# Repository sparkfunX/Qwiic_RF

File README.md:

# Qwiic_RF
LoRa Radio for the Qwiic System

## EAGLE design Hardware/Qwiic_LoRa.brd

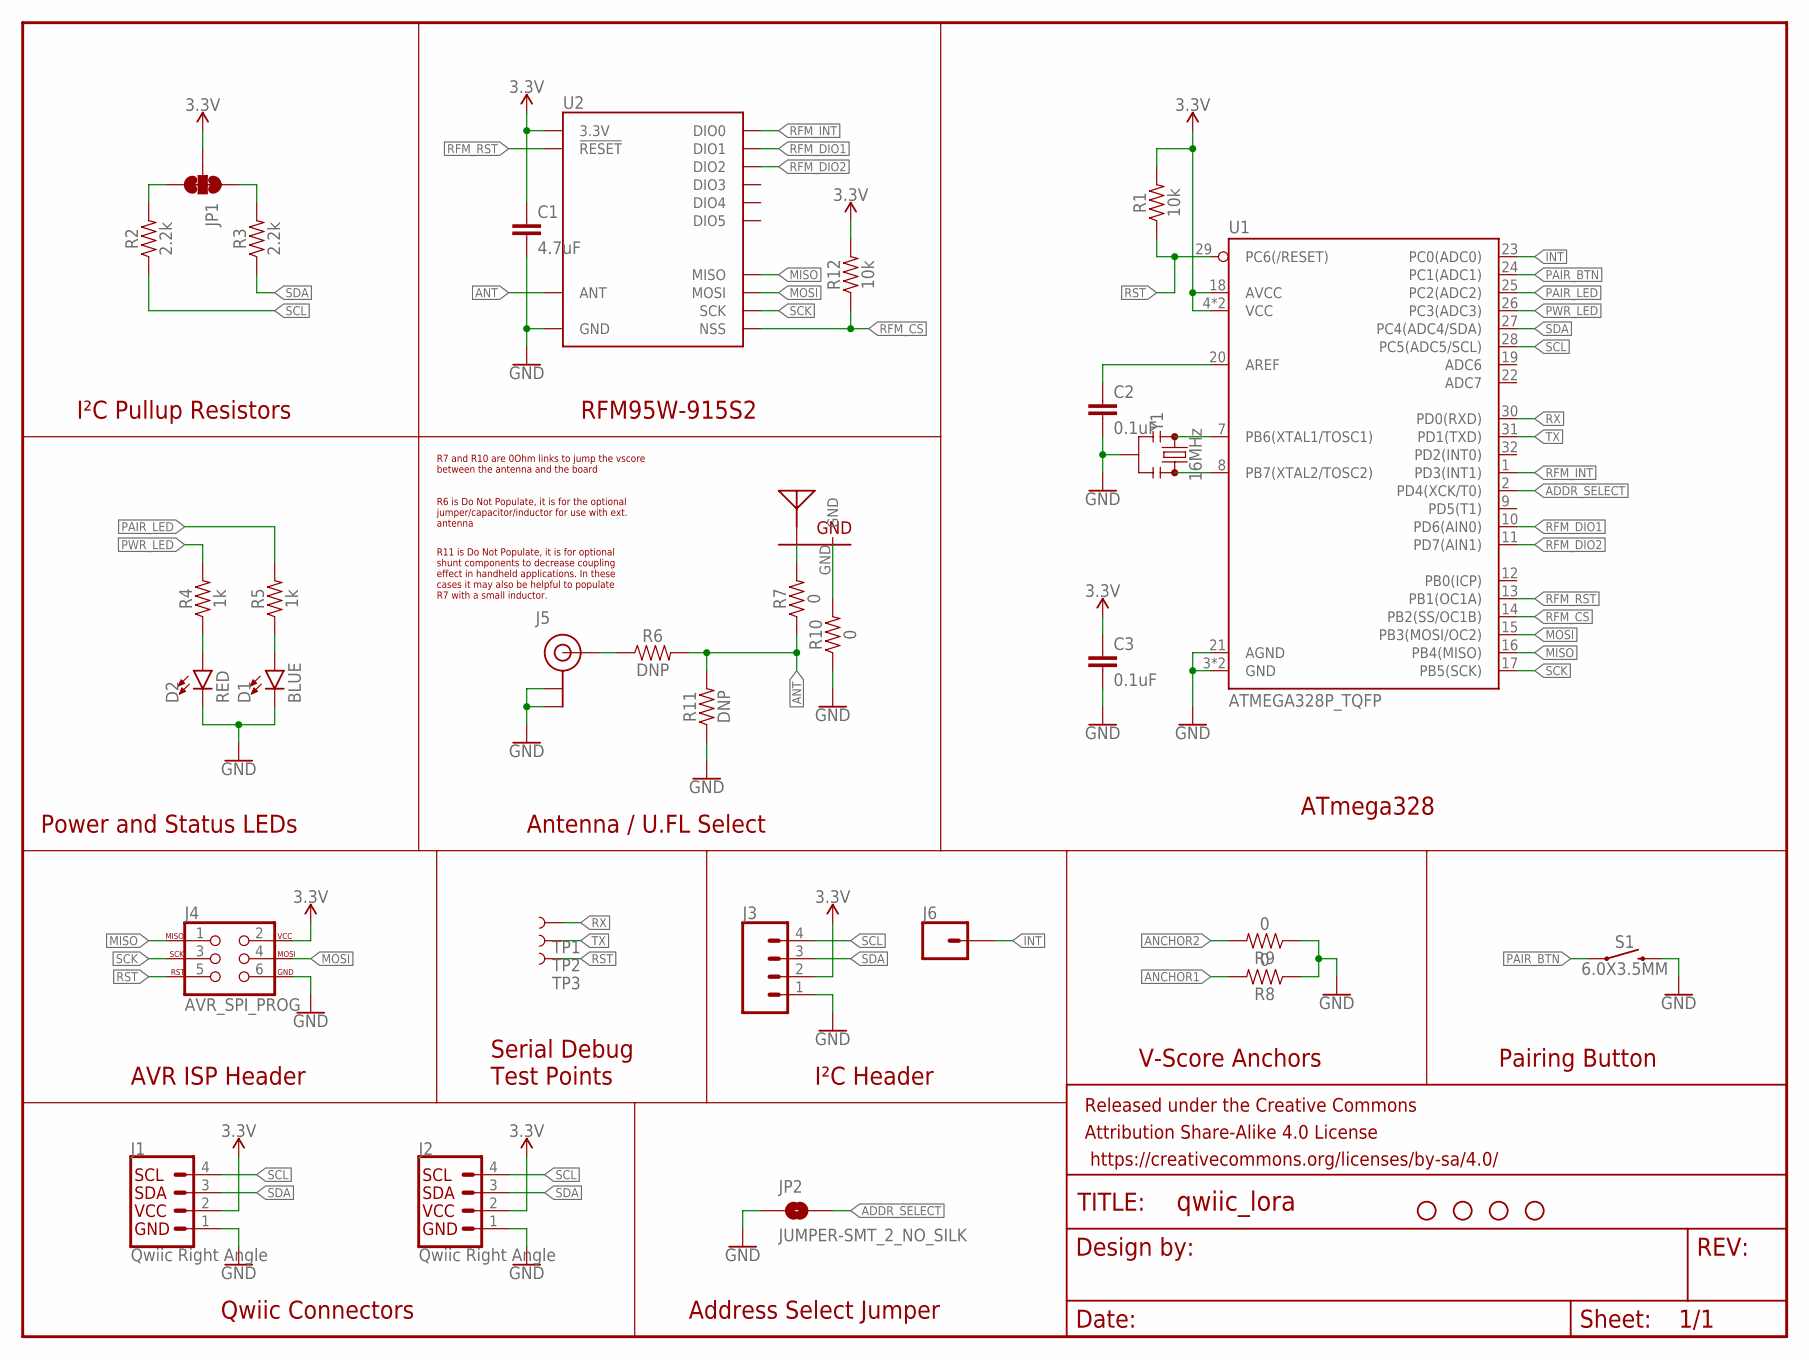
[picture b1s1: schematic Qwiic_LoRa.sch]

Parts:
C1: 4.7uF; 0603
C2, C3: 0.1uF; 0603
D1: BLUE; LED-0603
D2: RED; LED-0603
FRAME1: FRAME-LETTER; CREATIVE_COMMONS
H1, H2, H3, H4: STAND-OFF
J1, J2: Qwiic Right Angle; 1X04_1MM_RA
J3: CONN_041X04_NO_SILK; 1X04_NO_SILK
J4: AVR_SPI_PROG; 2X3_TEST_POINTS
J5: U.FL
J6: CONN_01PTH_NO_SILK_YES_STOP; 1X01_NO_SILK
JP1: JUMPER-SMT_3_2-NC_TRACE_SILK; SMT-JUMPER_3_2-NC_TRACE_SILK
JP2: JUMPER-SMT_2_NO_SILK; SMT-JUMPER_2_NO_SILK
R1, R12: 10k; 0603
R2, R3: 2.2k; 0603
R4, R5: 1k; 0603
R6, R11: DNP; 0603
R7, R8, R9, R10: 0; 0603
S1: 6.0X3.5MM; TACTILE_SWITCH_SMD_6.0X3.5MM
TP1, TP2, TP3: TEST-POINT3; PAD.03X.03
U1: ATMEGA328P_TQFP; TQFP32-08
U2: RFM96W; RFM95/96/97/98W
U$1: ANTENNA_915MHZ_INVERTED_F; ANTENNA_INVERTED_F_915MHZ
Y1: 16MHz; RESONATOR-SMD-3.2X1.3

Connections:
3.3V: C1.1, C3.1, J1.2, J2.2, J3.2, J4.2, JP1.2, R1.2, R12.2, U1.4 (VCC), U1.6 (VCC), U1.18 (AVCC), U2.3.3V
ADDR_SELECT: JP2.2, U1.2 (PD4(XCK/T0))
ANCHOR1: R8.2
ANCHOR2: R9.2
ANT: R6.2, R7.1, R11.2, U2.ANT
GND: C1.2, C2.2, C3.2, D1.C, D2.C, J1.1, J2.1, J3.1, J4.6, J5.1 (GND), J5.2 (GND), JP2.1, R8.1, R9.1, R10.1, R11.1, S1.2, U1.3 (GND), U1.5 (GND), U1.21 (AGND), U2.GND@1 (GND), U2.GND@2 (GND), U2.GND@3 (GND), Y1.2
INT: J6.1, U1.23 (PC0(ADC0))
MISO: J4.1, U1.16 (PB4(MISO)), U2.MISO
MOSI: J4.4, U1.15 (PB3(MOSI/OC2)), U2.MOSI
unnamed: D2.A, R4.1
unnamed: D1.A, R5.1
unnamed: C2.1, U1.20 (AREF)
unnamed: U1.7 (PB6(XTAL1/TOSC1)), Y1.1
unnamed: U1.8 (PB7(XTAL2/TOSC2)), Y1.3
unnamed: R7.2, U$1.FEED
unnamed: JP1.1, R3.2
unnamed: JP1.3, R2.2
unnamed: J5.FEED (SIGNAL), R6.1
unnamed: R10.2, U$1.GND
PAIR_BTN: S1.1, U1.24 (PC1(ADC1))
PAIR_LED: R5.2, U1.25 (PC2(ADC2))
PWR_LED: R4.2, U1.26 (PC3(ADC3))
RFM_CS: R12.1, U1.14 (PB2(SS/OC1B)), U2.NSS
RFM_DIO1: U1.10 (PD6(AIN0)), U2.DIO1
RFM_DIO2: U1.11 (PD7(AIN1)), U2.DIO2
RFM_INT: U1.1 (PD3(INT1)), U2.DIO0
RFM_RST: U1.13 (PB1(OC1A)), U2.!RESET
RST: J4.5, R1.1, TP3.P$1, U1.29 (PC6(/RESET))
RX: TP1.P$1, U1.30 (PD0(RXD))
SCK: J4.3, U1.17 (PB5(SCK)), U2.SCK
SCL: J1.4, J2.4, J3.4, R2.1, U1.28 (PC5(ADC5/SCL))
SDA: J1.3, J2.3, J3.3, R3.1, U1.27 (PC4(ADC4/SDA))
TX: TP2.P$1, U1.31 (PD1(TXD))

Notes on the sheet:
ATmega328
RFM95W-915S2
I²C Pullup Resistors
Antenna / U.FL Select
Power and Status LEDs
Qwiic Connectors
I²C Header
V-Score Anchors
Pairing Button
AVR ISP Header
Address Select Jumper
R7 and R10 are 0Ohm links to jump the vscore between the antenna and the board
R6 is Do Not Populate, it is for the optional jumper/capacitor/inductor for use with ext. antenna
R11 is Do Not Populate, it is for optional shunt components to decrease coupling effect in handheld applications. In these cases it may also be helpful to populate R7 with a small inductor.
Serial Debug Test Points

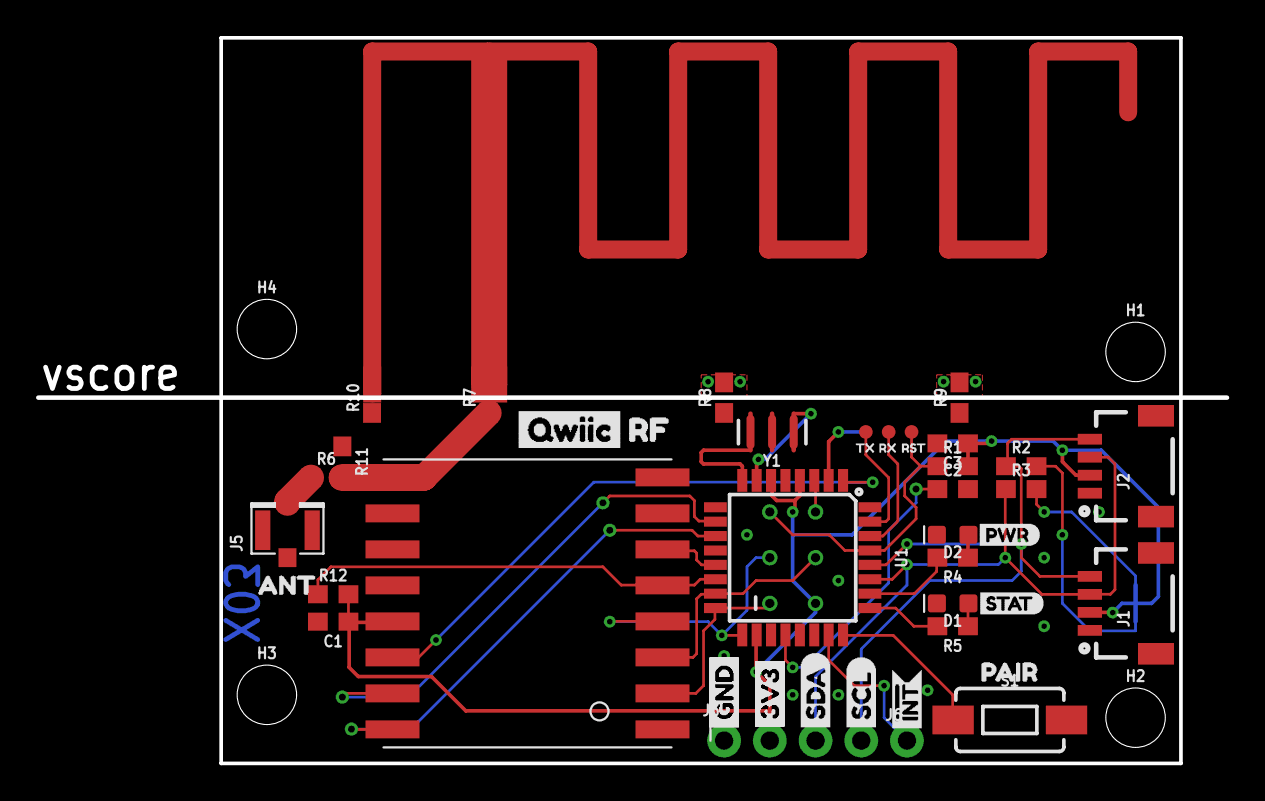
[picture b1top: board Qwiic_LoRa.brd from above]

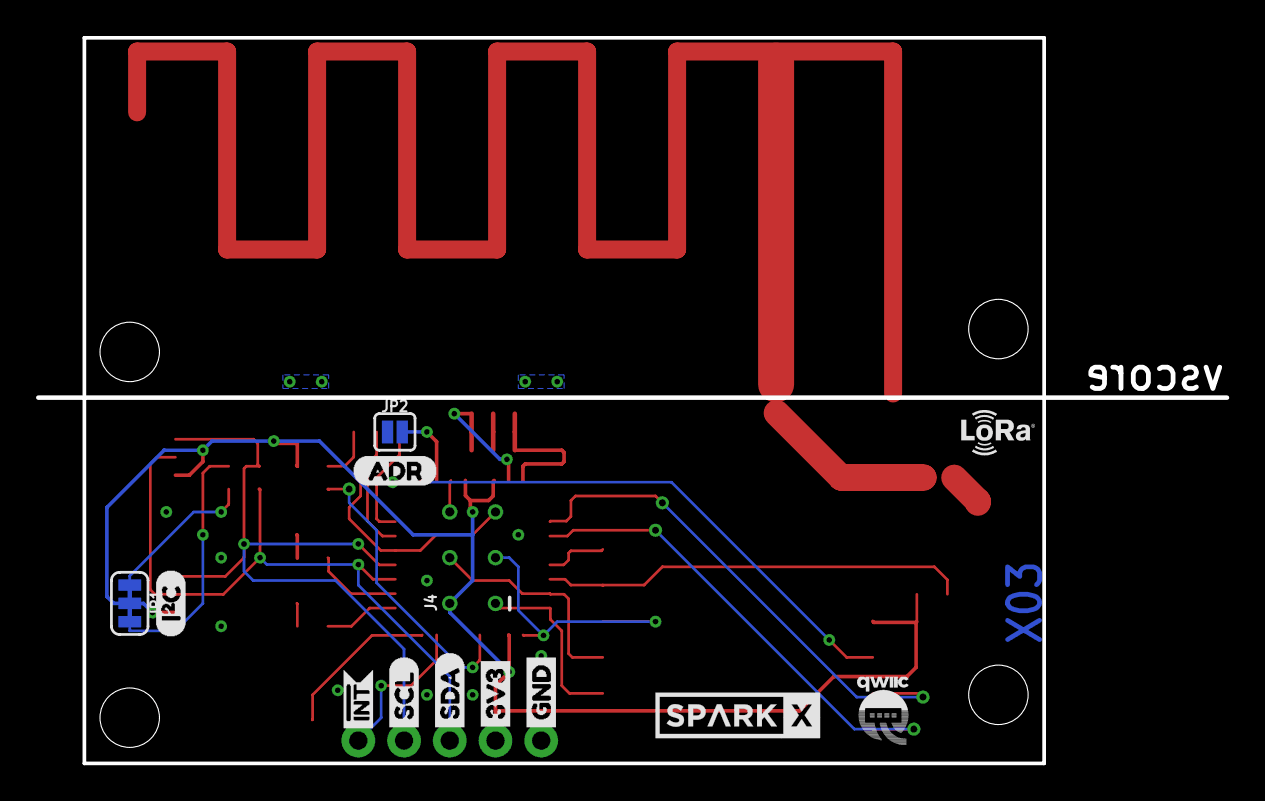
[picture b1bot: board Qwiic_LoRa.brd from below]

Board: 2 copper layers, 66.0 x 40.3 mm, 65 parts (13 on the bottom side), 31 nets.

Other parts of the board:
U$2: ANT0
U$3: PAIR1
U$4, U$22: SDA-[)
U$5, U$23: SCL-[)
U$6, U$18, U$19: GND-04
U$7, U$20, U$21: 3V3-04
U$8: PWR1
U$9: STAT2
U$10: QWIIC-LOGO-SMALL
U$11: TX1
U$12, U$24: INT#-[<
U$13: SPARKX-MEDIUM
U$14: ADR-()
U$15: RF1
U$16: QWIIC0
U$17: LORA_MARK#PNG
U$25: I_SUPER2_C-()-04
U$26: PRODUCTION_INSTRUCTIONS
U$27: RX0
U$28: RST2

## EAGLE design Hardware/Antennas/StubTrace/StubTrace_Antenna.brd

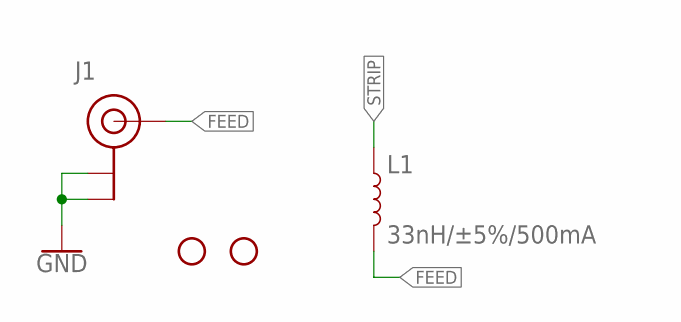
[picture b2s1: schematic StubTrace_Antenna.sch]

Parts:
H1, H2: STAND-OFF
J1: U.FL
L1: 33nH/±5%/500mA; 0603

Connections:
FEED: J1.FEED (SIGNAL), L1.2
GND: J1.1 (GND), J1.2 (GND)
STRIP: L1.1

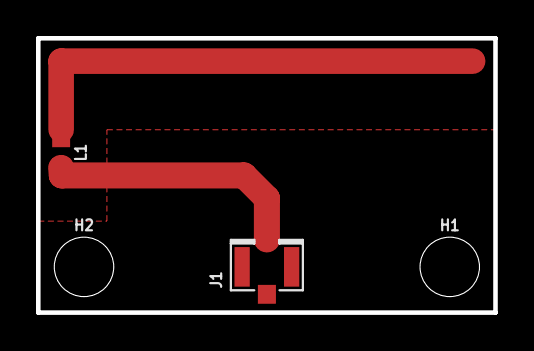
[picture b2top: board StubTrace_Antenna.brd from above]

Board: 2 copper layers, 25.4 x 15.2 mm, 4 parts (0 on the bottom side), 2 nets.

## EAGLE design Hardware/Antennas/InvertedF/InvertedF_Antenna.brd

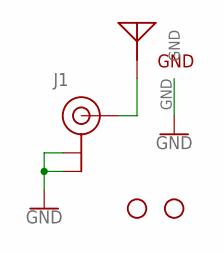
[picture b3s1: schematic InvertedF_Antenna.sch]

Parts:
H1, H2: STAND-OFF
J1: U.FL
U$1: ANTENNA_915MHZ_INVERTED_F; ANTENNA_INVERTED_F_915MHZ

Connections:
FEED: J1.FEED (SIGNAL), U$1.FEED
GND: J1.1 (GND), J1.2 (GND), U$1.GND

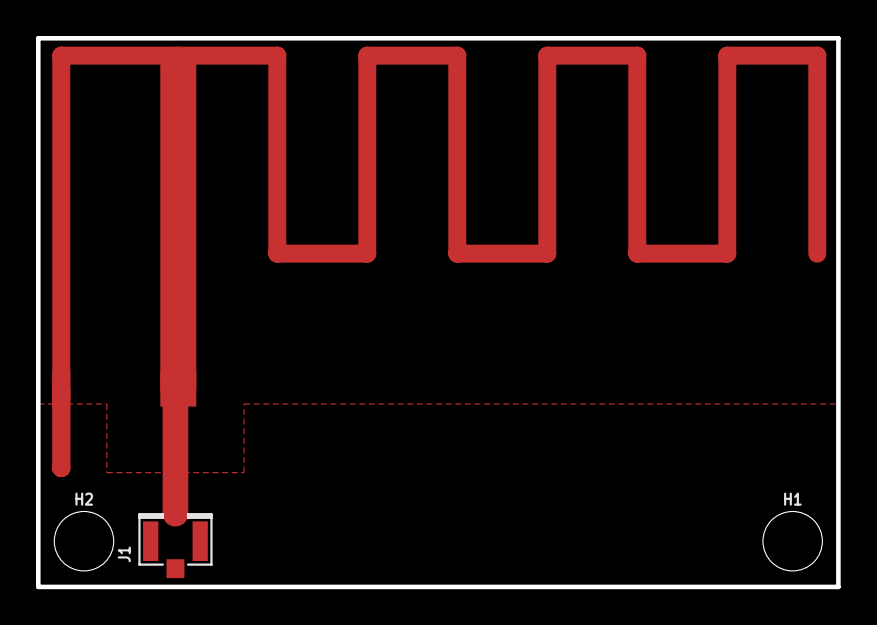
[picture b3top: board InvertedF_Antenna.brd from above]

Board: 2 copper layers, 44.5 x 30.5 mm, 4 parts (0 on the bottom side), 2 nets.

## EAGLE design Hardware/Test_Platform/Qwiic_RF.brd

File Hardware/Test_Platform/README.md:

** Test Platform for Qwiic LoRa **

This is essentially the prototype Qwiic LoRa hardware with only a U.FL connector for testing modular antennas for integration.

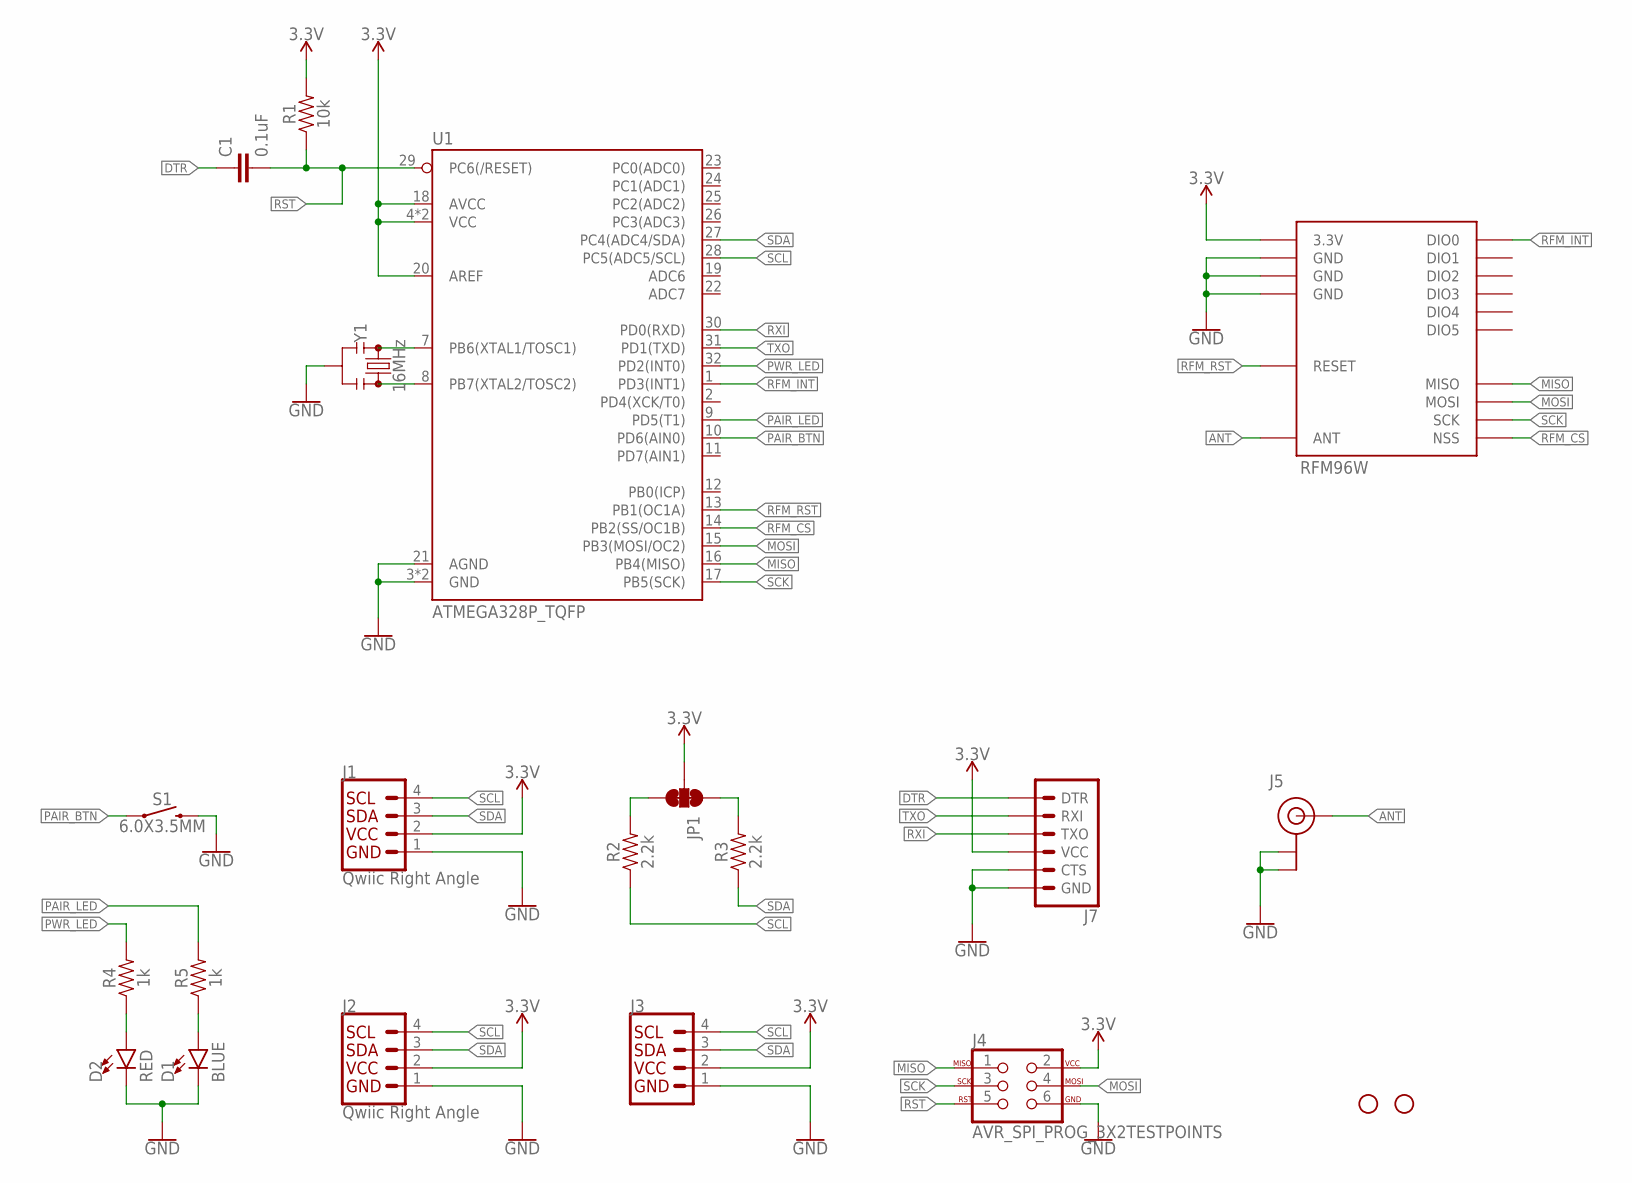
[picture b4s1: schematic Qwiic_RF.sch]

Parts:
C1: 0.1uF; 0603
D1: BLUE; LED-0603
D2: RED; LED-0603
H1, H2: STAND-OFF
J1, J2: Qwiic Right Angle; 1X04_1MM_RA
J3: I2C_STANDARD; 1X04
J4: AVR_SPI_PROG_3X2TESTPOINTS; 2X3_TEST_POINTS
J5: U.FL
J7: 6_PIN_SERIAL_TARGET; 1X06
JP1: JUMPER-SMT_3_2-NC_TRACE_SILK; SMT-JUMPER_3_2-NC_TRACE_SILK
R1: 10k; 0603
R2, R3: 2.2k; 0603
R4, R5: 1k; 0603
RFM96W: RFM96W; RFM95/96/97/98W
S1: 6.0X3.5MM; TACTILE_SWITCH_SMD_6.0X3.5MM
U1: ATMEGA328P_TQFP; TQFP32-08
Y1: 16MHz; RESONATOR-SMD-3.2X1.3

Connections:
3.3V: J1.2, J2.2, J3.2, J4.2, J7.4 (VCC), JP1.2, R1.2, RFM96W.3.3V, U1.4 (VCC), U1.6 (VCC), U1.18 (AVCC), U1.20 (AREF)
ANT: J5.FEED (SIGNAL), RFM96W.ANT
DTR: C1.1, J7.1 (DTR)
GND: D1.C, D2.C, J1.1, J2.1, J3.1, J4.6, J5.1 (GND), J5.2 (GND), J7.5 (CTS), J7.6 (GND), RFM96W.GND@1 (GND), RFM96W.GND@2 (GND), RFM96W.GND@3 (GND), S1.2, U1.3 (GND), U1.5 (GND), U1.21 (AGND), Y1.2
MISO: J4.1, RFM96W.MISO, U1.16 (PB4(MISO))
MOSI: J4.4, RFM96W.MOSI, U1.15 (PB3(MOSI/OC2))
unnamed: D2.A, R4.1
unnamed: D1.A, R5.1
unnamed: U1.7 (PB6(XTAL1/TOSC1)), Y1.1
unnamed: U1.8 (PB7(XTAL2/TOSC2)), Y1.3
unnamed: JP1.1, R3.2
unnamed: JP1.3, R2.2
PAIR_BTN: S1.1, U1.10 (PD6(AIN0))
PAIR_LED: R5.2, U1.9 (PD5(T1))
PWR_LED: R4.2, U1.32 (PD2(INT0))
RFM_CS: RFM96W.NSS, U1.14 (PB2(SS/OC1B))
RFM_INT: RFM96W.DIO0, U1.1 (PD3(INT1))
RFM_RST: RFM96W.RESET, U1.13 (PB1(OC1A))
RST: C1.2, J4.5, R1.1, U1.29 (PC6(/RESET))
RXI: J7.3 (TXO), U1.30 (PD0(RXD))
SCK: J4.3, RFM96W.SCK, U1.17 (PB5(SCK))
SCL: J1.4, J2.4, J3.4, R2.1, U1.28 (PC5(ADC5/SCL))
SDA: J1.3, J2.3, J3.3, R3.1, U1.27 (PC4(ADC4/SDA))
TXO: J7.2 (RXI), U1.31 (PD1(TXD))

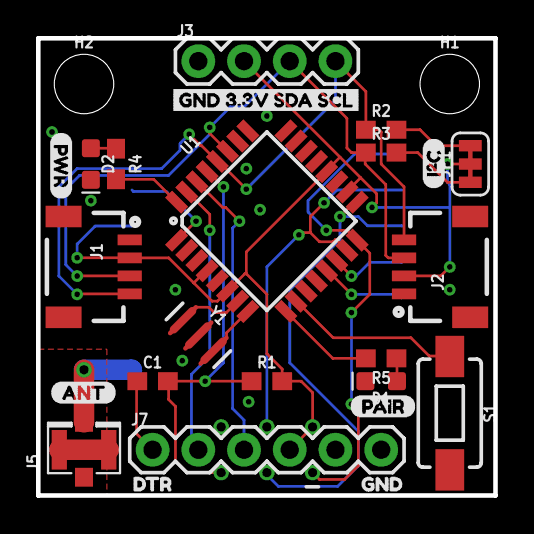
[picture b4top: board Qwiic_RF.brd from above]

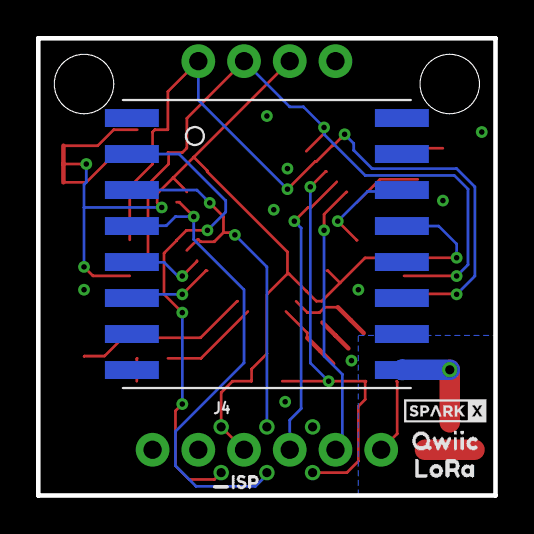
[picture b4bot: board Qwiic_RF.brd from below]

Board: 2 copper layers, 25.4 x 25.4 mm, 32 parts (6 on the bottom side), 24 nets.

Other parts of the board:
U$1: ANT5
U$2: DTR3
U$3: GND4
U$4: GND_3#3V_SDA_SCL6
U$5: I#C2
U$6: PAIR1
U$7: PWR0
U$8: SPARKX-TINY
U$9: QWIIC0
U$10: LORA1
U$11: ISP0

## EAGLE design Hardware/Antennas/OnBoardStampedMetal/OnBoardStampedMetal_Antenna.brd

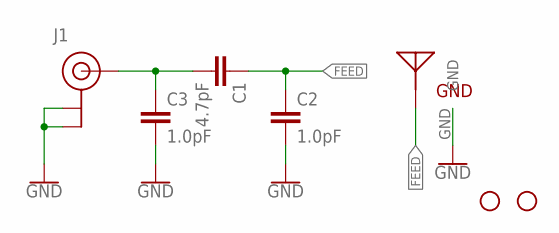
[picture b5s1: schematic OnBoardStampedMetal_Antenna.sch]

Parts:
C1: 4.7pF; 0603
C2, C3: 1.0pF; 0603
H1, H2: STAND-OFF
J1: U.FL
U$1: ONBOARD_SMD_STAMPED

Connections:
FEED: C1.1, C2.1, U$1.FEED
GND: C2.2, C3.2, J1.1 (GND), J1.2 (GND), U$1.GND
unnamed: C1.2, C3.1, J1.FEED (SIGNAL)

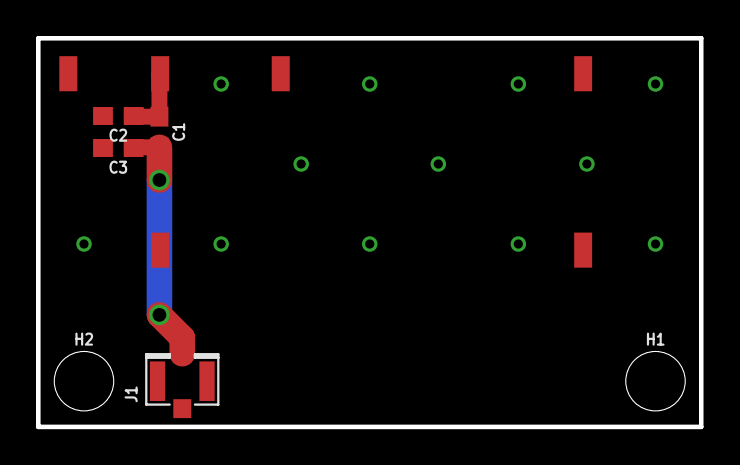
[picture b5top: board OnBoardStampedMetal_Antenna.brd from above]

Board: 2 copper layers, 36.8 x 21.6 mm, 7 parts (0 on the bottom side), 3 nets.

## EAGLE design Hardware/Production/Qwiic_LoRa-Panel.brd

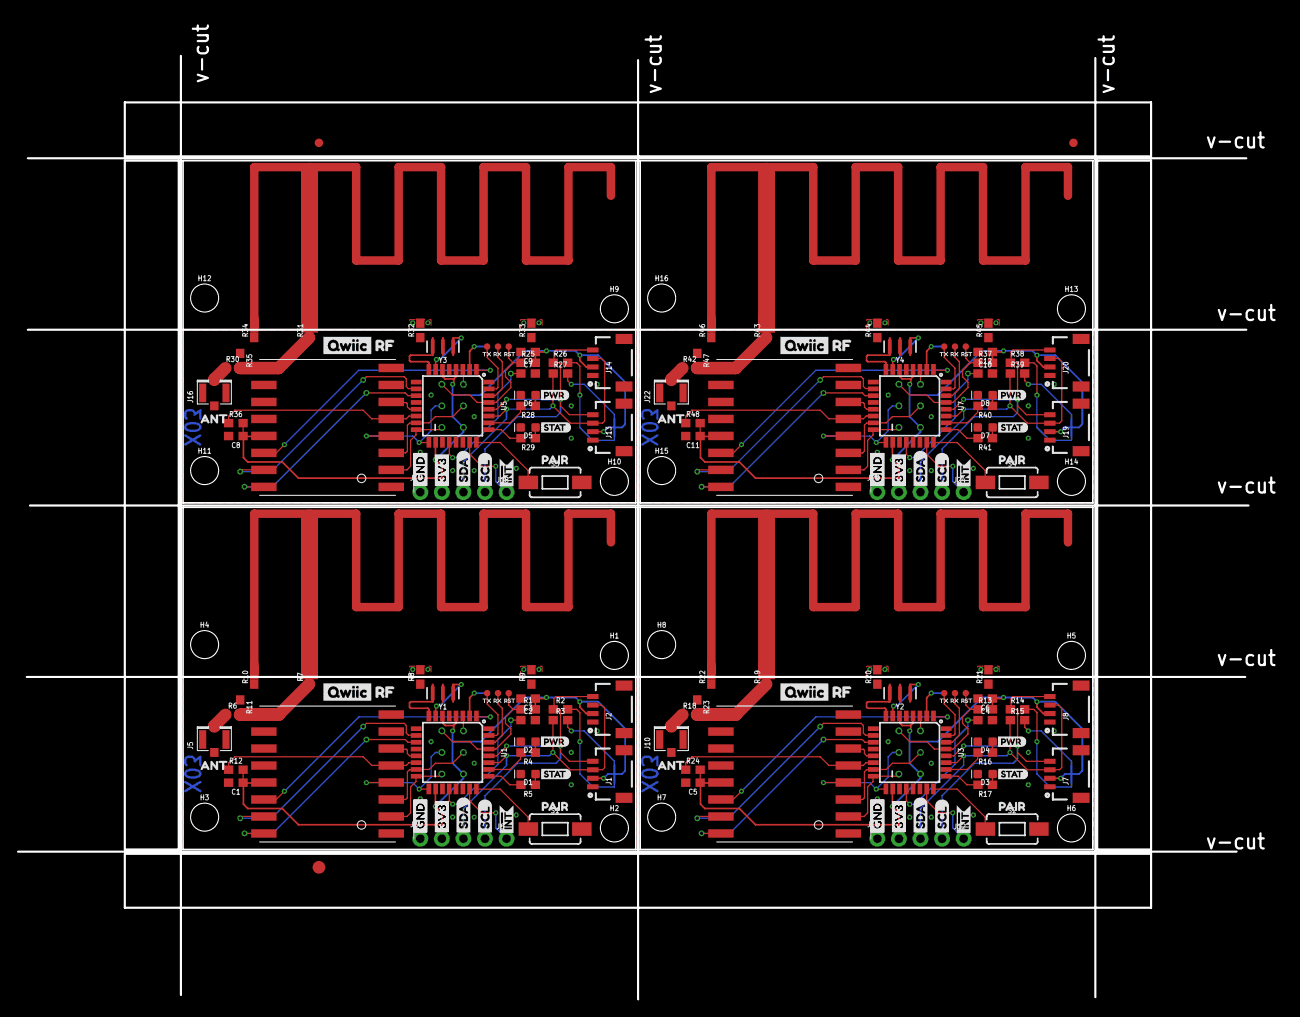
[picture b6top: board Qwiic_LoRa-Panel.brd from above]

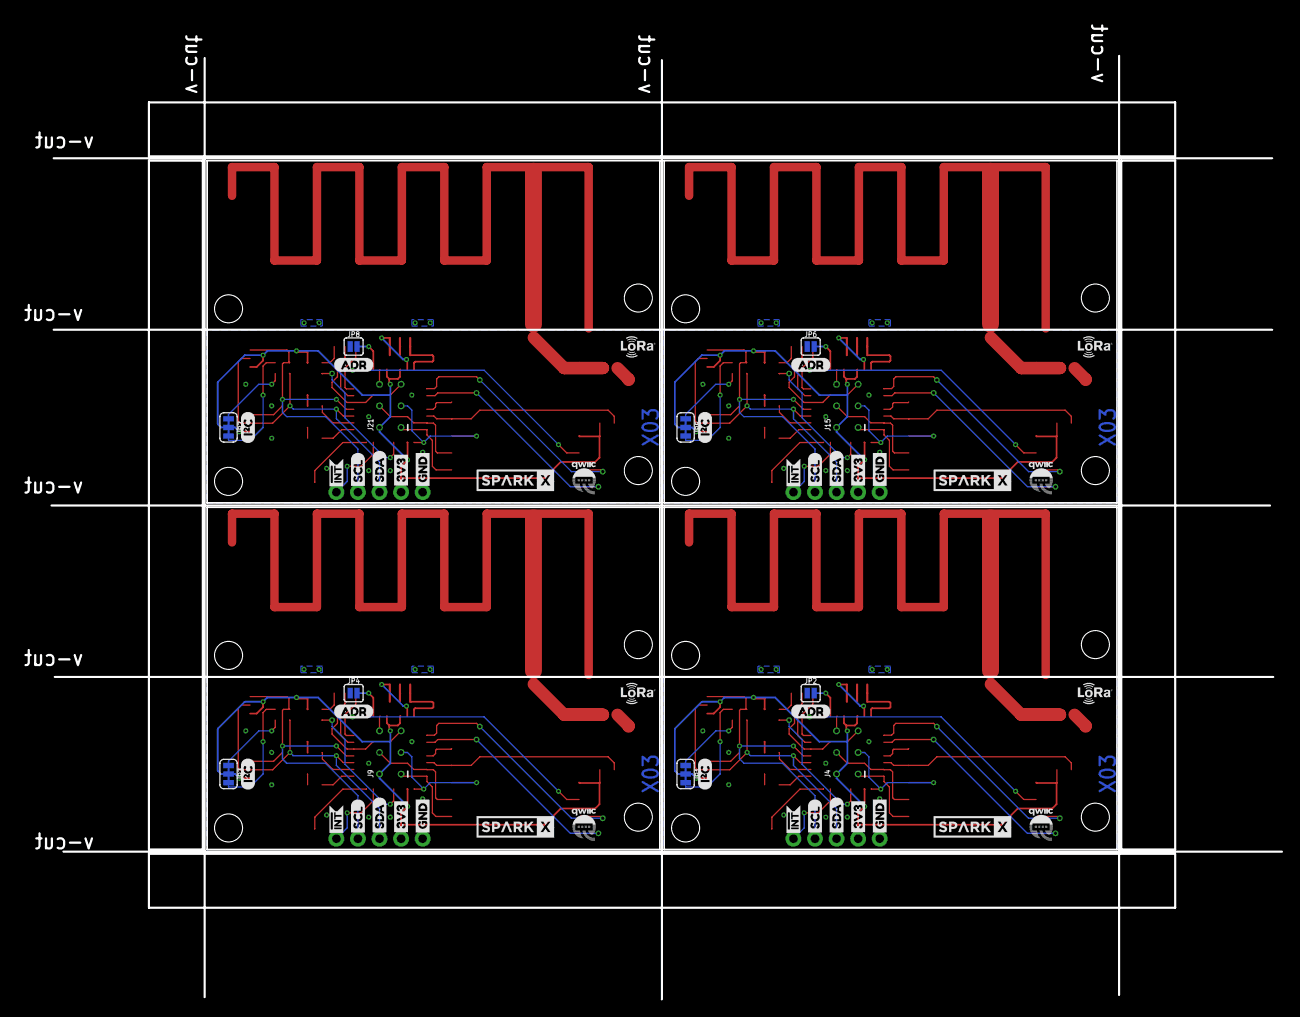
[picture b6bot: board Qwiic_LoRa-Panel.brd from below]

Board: 2 copper layers, 148.8 x 115.6 mm, 255 parts (52 on the bottom side), 124 nets.

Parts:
C1, C5, C8, C11: 4.7uF; 0603
C2, C3, C4, C6, C7, C9, C10, C12: 0.1uF; 0603
D1, D3, D5, D7: BLUE; LED-0603
D2, D4, D6, D8: RED; LED-0603
E$1, E$2: FIDUCIAL-1X2
E$3: FIDUCIAL-1.5X3
H1, H2, H3, H4, H5, H6, H7, H8, H9, H10, H11, H12, H13, H14, H15, H16: STAND-OFF
J1, J2, J7, J8, J13, J14, J19, J20: Qwiic Right Angle; 1X04_1MM_RA
J3, J11, J17, J23: 1X04_NO_SILK
J4, J9, J15, J21: AVR_SPI_PROG; 2X3_TEST_POINTS
J5, J10, J16, J22: U.FL
J6, J12, J18, J24: 1X01_NO_SILK
JP1, JP3, JP5, JP7: SMT-JUMPER_3_2-NC_TRACE_SILK
JP2, JP4, JP6, JP8: JUMPER-SMT_2_NO_SILK; SMT-JUMPER_2_NO_SILK
R1, R12, R13, R24, R25, R36, R37, R48: 10k; 0603
R2, R3, R14, R15, R26, R27, R38, R39: 2.2k; 0603
R4, R5, R16, R17, R28, R29, R40, R41: 1k; 0603
R6, R11, R18, R23, R30, R35, R42, R47: DNP; 0603
R7, R8, R9, R10, R19, R20, R21, R22, R31, R32, R33, R34, R43, R44, R45, R46: 0; 0603
S1, S2, S3, S4: 6.0X3.5MM; TACTILE_SWITCH_SMD_6.0X3.5MM
TP1, TP2, TP3, TP4, TP5, TP6, TP7, TP8, TP9, TP10, TP11, TP12: PAD.03X.03
U1, U3, U5, U7: ATMEGA328P_TQFP; TQFP32-08
U2, U4, U6, U8: RFM96W; RFM95/96/97/98W
U$1, U$26, U$55, U$82: ANTENNA_915MHZ_INVERTED_F; ANTENNA_INVERTED_F_915MHZ
U$2, U$50, U$77, U$104: ANT0
U$3, U$51, U$78, U$105: PAIR1
U$4, U$22, U$29, U$42, U$56, U$69, U$83, U$96: SDA-[)
U$5, U$23, U$30, U$43, U$57, U$70, U$84, U$97: SCL-[)
U$6, U$18, U$19, U$31, U$38, U$39, U$58, U$65, U$66, U$85, U$92, U$93: GND-04
U$7, U$20, U$21, U$32, U$40, U$41, U$59, U$67, U$68, U$86, U$94, U$95: 3V3-04
U$8, U$33, U$60, U$87: PWR1
U$9, U$34, U$61, U$88: STAT2
U$10, U$48, U$75, U$102: QWIIC-LOGO-SMALL
U$11, U$52, U$79, U$106: TX1
U$12, U$24, U$37, U$44, U$64, U$71, U$91, U$98: INT#-[<
U$13, U$36, U$63, U$90: SPARKX-MEDIUM
U$14, U$45, U$72, U$99: ADR-()
U$15, U$47, U$74, U$101: RF1
U$16, U$35, U$62, U$89: QWIIC0
U$17, U$49, U$76, U$103: LORA_MARK#PNG
U$25, U$46, U$73, U$100: I_SUPER2_C-()-04
U$27, U$53, U$80, U$107: RX0
U$28, U$54, U$81, U$108: RST2
Y1, Y2, Y3, Y4: 16MHz; RESONATOR-SMD-3.2X1.3

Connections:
3.3V: C1.1, C3.1, J1.2, J2.2, J3.2, J4.2, JP1.2, R1.2, R12.2, U1.4, U1.6, U1.18, U2.3.3V
3.3V1: C5.1, C6.1, J7.2, J8.2, J9.2, J11.2, JP3.2, R13.2, R24.2, U3.4, U3.6, U3.18, U4.3.3V
3.3V2: C8.1, C9.1, J13.2, J14.2, J15.2, J17.2, JP5.2, R25.2, R36.2, U5.4, U5.6, U5.18, U6.3.3V
3.3V3: C11.1, C12.1, J19.2, J20.2, J21.2, J23.2, JP7.2, R37.2, R48.2, U7.4, U7.6, U7.18, U8.3.3V
ADDR_SELECT: JP2.2, U1.2
ADDR_SELECT1: JP4.2, U3.2
ADDR_SELECT2: JP6.2, U5.2
ADDR_SELECT3: JP8.2, U7.2
ANT: R6.2, R7.1, R11.2, U2.ANT
ANT1: R18.2, R19.1, R23.2, U4.ANT
ANT2: R30.2, R31.1, R35.2, U6.ANT
ANT3: R42.2, R43.1, R47.2, U8.ANT
GND: C1.2, C2.2, C3.2, D1.C, D2.C, J1.1, J2.1, J3.1, J4.6, J5.1, J5.2, JP2.1, R8.1, R9.1, R10.1, R11.1, S1.2, U1.3, U1.5, U1.21, U2.GND@1, U2.GND@2, U2.GND@3, Y1.2
GND1: C4.2, C5.2, C6.2, D3.C, D4.C, J7.1, J8.1, J9.6, J10.1, J10.2, J11.1, JP4.1, R20.1, R21.1, R22.1, R23.1, S2.2, U3.3, U3.5, U3.21, U4.GND@1, U4.GND@2, U4.GND@3, Y2.2
GND2: C7.2, C8.2, C9.2, D5.C, D6.C, J13.1, J14.1, J15.6, J16.1, J16.2, J17.1, JP6.1, R32.1, R33.1, R34.1, R35.1, S3.2, U5.3, U5.5, U5.21, U6.GND@1, U6.GND@2, U6.GND@3, Y3.2
GND3: C10.2, C11.2, C12.2, D7.C, D8.C, J19.1, J20.1, J21.6, J22.1, J22.2, J23.1, JP8.1, R44.1, R45.1, R46.1, R47.1, S4.2, U7.3, U7.5, U7.21, U8.GND@1, U8.GND@2, U8.GND@3, Y4.2
INT: J6.1, U1.23
INT1: J12.1, U3.23
INT2: J18.1, U5.23
INT3: J24.1, U7.23
MISO: J4.1, U1.16, U2.MISO
MISO1: J9.1, U3.16, U4.MISO
MISO2: J15.1, U5.16, U6.MISO
MISO3: J21.1, U7.16, U8.MISO
MOSI: J4.4, U1.15, U2.MOSI
MOSI1: J9.4, U3.15, U4.MOSI
MOSI2: J15.4, U5.15, U6.MOSI
MOSI3: J21.4, U7.15, U8.MOSI
unnamed: D2.A, R4.1
unnamed: D1.A, R5.1
unnamed: C2.1, U1.20
unnamed: U1.7, Y1.1
unnamed: U1.8, Y1.3
unnamed: R7.2, U$1.FEED
unnamed: JP1.1, R3.2
unnamed: JP1.3, R2.2
unnamed: J5.FEED, R6.1
unnamed: U3.7, Y2.1
unnamed: R10.2, U$1.GND
unnamed: U3.8, Y2.3
unnamed: JP3.1, R15.2
unnamed: JP3.3, R14.2
unnamed: D4.A, R16.1
unnamed: D3.A, R17.1
unnamed: J10.FEED, R18.1
unnamed: C4.1, U3.20
unnamed: R19.2, U$26.FEED
unnamed: R22.2, U$26.GND
unnamed: U5.7, Y3.1
unnamed: U5.8, Y3.3
unnamed: JP5.1, R27.2
unnamed: JP5.3, R26.2
unnamed: D6.A, R28.1
unnamed: D5.A, R29.1
unnamed: J16.FEED, R30.1
unnamed: C7.1, U5.20
unnamed: R31.2, U$55.FEED
unnamed: R34.2, U$55.GND
unnamed: U7.7, Y4.1
unnamed: U7.8, Y4.3
unnamed: JP7.1, R39.2
unnamed: JP7.3, R38.2
unnamed: D8.A, R40.1
unnamed: D7.A, R41.1
unnamed: J22.FEED, R42.1
unnamed: C10.1, U7.20
unnamed: R43.2, U$82.FEED
unnamed: R46.2, U$82.GND
PAIR_BTN: S1.1, U1.24
PAIR_BTN1: S2.1, U3.24
PAIR_BTN2: S3.1, U5.24
PAIR_BTN3: S4.1, U7.24
PAIR_LED: R5.2, U1.25
PAIR_LED1: R17.2, U3.25
PAIR_LED2: R29.2, U5.25
PAIR_LED3: R41.2, U7.25
PWR_LED: R4.2, U1.26
PWR_LED1: R16.2, U3.26
PWR_LED2: R28.2, U5.26
PWR_LED3: R40.2, U7.26
RFM_CS: R12.1, U1.14, U2.NSS
RFM_CS1: R24.1, U3.14, U4.NSS
RFM_CS2: R36.1, U5.14, U6.NSS
RFM_CS3: R48.1, U7.14, U8.NSS
RFM_DIO1: U1.10, U2.DIO1
RFM_DIO2: U1.11, U2.DIO2
RFM_DIO3: U3.10, U4.DIO1
RFM_DIO4: U3.11, U4.DIO2
RFM_DIO5: U5.10, U6.DIO1
RFM_DIO6: U5.11, U6.DIO2
RFM_DIO7: U7.10, U8.DIO1
RFM_DIO8: U7.11, U8.DIO2
RFM_INT: U1.1, U2.DIO0
RFM_INT1: U3.1, U4.DIO0
RFM_INT2: U5.1, U6.DIO0
RFM_INT3: U7.1, U8.DIO0
RFM_RST: U1.13, U2.!RESET
RFM_RST1: U3.13, U4.!RESET
RFM_RST2: U5.13, U6.!RESET
RFM_RST3: U7.13, U8.!RESET
RST: J4.5, R1.1, TP3.P$1, U1.29
RST1: J9.5, R13.1, TP6.P$1, U3.29
RST2: J15.5, R25.1, TP9.P$1, U5.29
RST3: J21.5, R37.1, TP12.P$1, U7.29
RX: TP1.P$1, U1.30
RX1: TP4.P$1, U3.30
RX2: TP7.P$1, U5.30
RX3: TP10.P$1, U7.30
SCK: J4.3, U1.17, U2.SCK
SCK1: J9.3, U3.17, U4.SCK
SCK2: J15.3, U5.17, U6.SCK
SCK3: J21.3, U7.17, U8.SCK
SCL: J1.4, J2.4, J3.4, R2.1, U1.28
SCL1: J7.4, J8.4, J11.4, R14.1, U3.28
SCL2: J13.4, J14.4, J17.4, R26.1, U5.28
SCL3: J19.4, J20.4, J23.4, R38.1, U7.28
SDA: J1.3, J2.3, J3.3, R3.1, U1.27
SDA1: J7.3, J8.3, J11.3, R15.1, U3.27
SDA2: J13.3, J14.3, J17.3, R27.1, U5.27
SDA3: J19.3, J20.3, J23.3, R39.1, U7.27
TX: TP2.P$1, U1.31
TX1: TP5.P$1, U3.31
TX2: TP8.P$1, U5.31
TX3: TP11.P$1, U7.31

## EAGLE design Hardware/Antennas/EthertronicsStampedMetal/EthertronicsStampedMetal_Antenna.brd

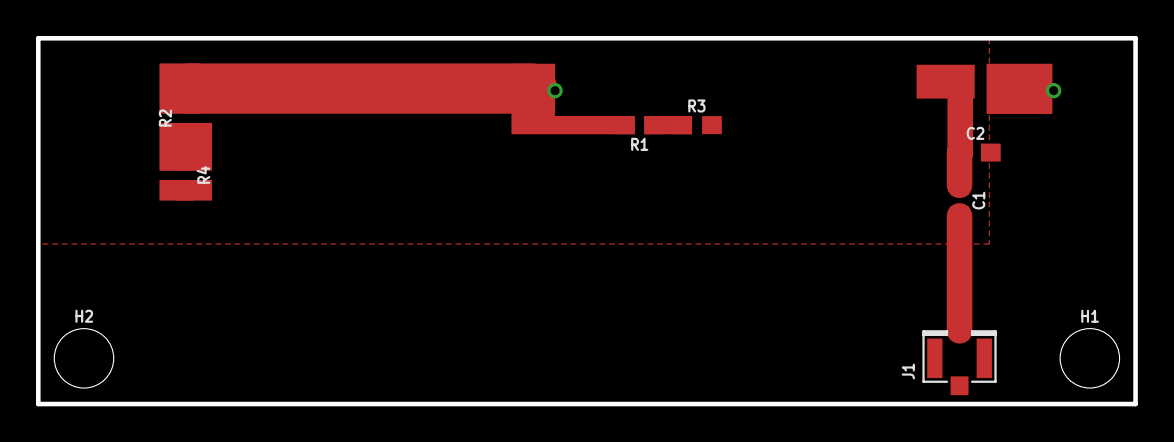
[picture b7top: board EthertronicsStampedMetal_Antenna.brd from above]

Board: 2 copper layers, 61.0 x 20.3 mm, 10 parts (0 on the bottom side), 6 nets.

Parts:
C1: 4.7pF; 0603
C2: 1.0pF; 0603
H1, H2: STAND-OFF
J1: U.FL
R1, R2, R3, R4: 0; 0603
U$1: ETHERTRONICS_STAMPED_ANTENNA; ETHERTRONICS_ISM_STAMPED

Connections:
FEED: C1.1, C2.1, U$1.FEED
GND: C2.2, J1.1, J1.2, U$1.GND
unnamed: C1.2, J1.FEED
unnamed: R2.1, R4.1
unnamed: R1.1, R3.1
STRIP: R1.2, R4.2

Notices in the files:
parts and their libraries:
SparkFun-Connectors: Licensing: Creative Commons ShareAlike 4.0 International - https://creativecommons.org/licenses/by-sa/4.0
SparkFun-Aesthetics: Released under the Creative Commons Attribution Share-Alike 4.0 License
SparkFun-Aesthetics: https://creativecommons.org/licenses/by-sa/4.0
